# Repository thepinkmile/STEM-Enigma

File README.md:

# STEM-Enigma
A repository containing data, designs and software for an Enigma Machine.

## Interactive 3D Enigma

The existing [Code Breakers application](Software/APP-CodeBreakers/src/CodeBreakers/README.md)
uses Avalonia and TinyFFR to animate rotor gears, trace electrical connections,
and switch between assembled and exploded views. Original part models and
their generator are included.

With the .NET 10 SDK installed:

```powershell
Set-Location Software\APP-CodeBreakers\src
dotnet run --project CodeBreakers.Desktop
```

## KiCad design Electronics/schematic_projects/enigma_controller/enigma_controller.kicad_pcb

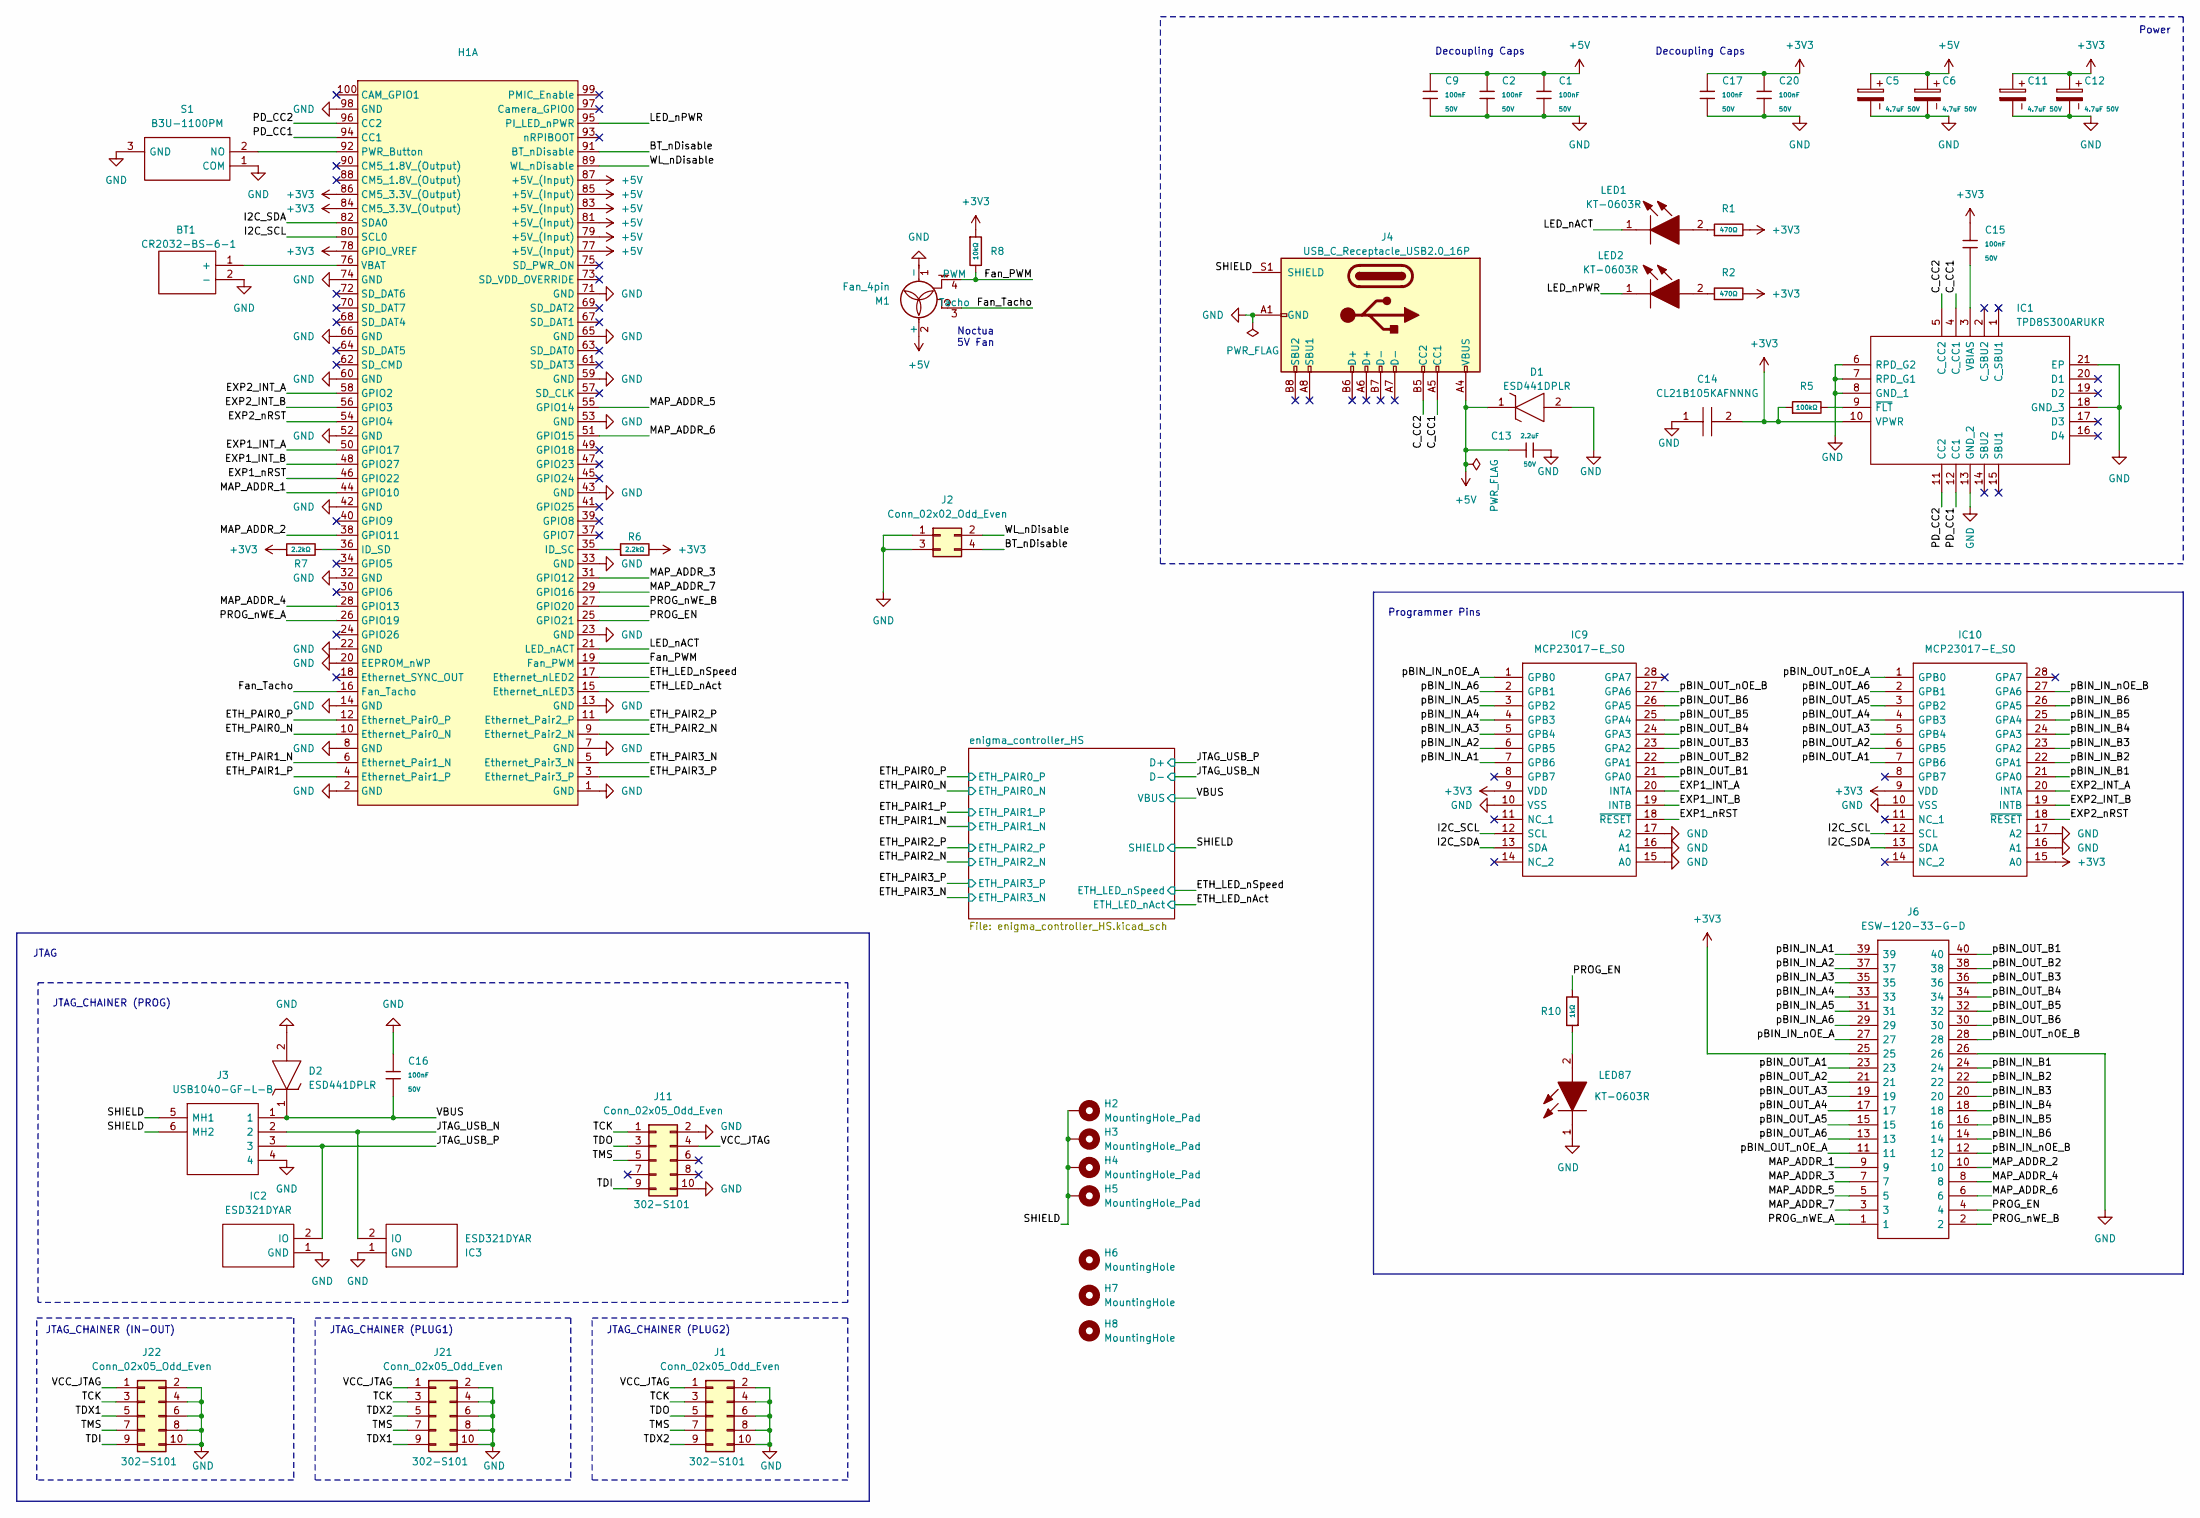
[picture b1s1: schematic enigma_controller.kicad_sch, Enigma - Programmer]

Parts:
BT1: CR2032-BS-6-1; CR2032BS61; Manufacturer_Part_Number CR2032-BS-6-1
C1, C2, C9, C15, C16, C17, C20: 100nF; C_0402; Voltage Rated 50V; Tolerance ±10%; Part CL05B104KB54PNC; LCSC C307331
C5, C6, C11, C12: 4.7uF 50V; CP_Radial_D5.0mm_P2.00mm
C13: 2.2uF; C_1206; Voltage Rated 50V; Tolerance ±10%; Part CL31B225KBHNNNE; LCSC C50254
C14: CL21B105KAFNNNG; CAPC2012X135N; Manufacturer_Part_Number CL21B105KAFNNNG; Mouser Part Number 187-CL21B105KAFNNNG
D1, D2: ESD441DPLR; Manufacturer_Part_Number ESD441DPLR; Mouser Part Number 595-ESD441DPLR
H1: RaspberryPi-CM5-Carrier-Tall-Pad-Via-Standoff
H2, H3, H4, H5: MountingHole_Pad; MountingHole_4.3mm_M4_Pad_Via
H6, H7, H8: MountingHole; MountingHole_4.3mm_M4
IC1: TPD8S300ARUKR; QFN40P300X300X80-21N-D; Manufacturer_Part_Number TPD8S300ARUKR; Mouser Part Number 595-TPD8S300ARUKR
IC2, IC3: ESD321DYAR; SODFL1608X77N; Manufacturer_Part_Number ESD321DYAR; Mouser Part Number 595-ESD321DYAR
IC9, IC10: MCP23017-E_SO; SOIC127P1030X265-28N; Manufacturer_Part_Number MCP23017-E/SO; Mouser Part Number 579-MCP23017-E/SO
J1, J21, J22: Conn_02x05_Odd_Even; IDC-Header_2x05_P2.54mm_Horizontal; Part No 302-S101; DigiKey Part No ED1543-ND
J2: Conn_02x02_Odd_Even; PinHeader_2x02_P2.54mm_Vertical
J3: USB1040-GF-L-B; USB1040GFLB; Manufacturer_Part_Number USB1040-GF-L-B; Mouser Part Number 640-USB1040-GF-L-B
J4: USB_C_Receptacle_USB2.0_16P; USB_C_Receptacle_Amphenol_124019772112A; LCSC C5430474
J6: ESW-120-33-G-D; ESW-120-XX-Y-D; Manufacturer_Part_Number ESW-120-33-G-D; Mouser Part Number 200-ESW12033GD
J11: Conn_02x05_Odd_Even; IDC-Header_2x05_P2.54mm_Vertical; Part No 302-S101; DigiKey Part No ED1543-ND
LED1, LED2, LED87: KT-0603R; LEDC1608X70N; Manufacturer_Part_Number KT-0603R
M1: Fan_4pin; FanPinHeader_1x04_P2.54mm_Vertical
R1, R2: 470Ω; R_0402; Overload Voltage (Max) 50V; Tolerance ±1%; Part 0402WGF4700TCE; LCSC C25117
R5: 100kΩ; R_0402; Overload Voltage (Max) 50V; Tolerance ±1%; Part 0402WGF1003TCE; LCSC C25741
R6, R7: 2.2kΩ; R_0402; Overload Voltage (Max) 50V; Tolerance ±1%; Part 0402WGF2201TCE; LCSC C25879
R8: 10kΩ; R_0402; Overload Voltage (Max) 50V; Tolerance ±1%; Part 0402WGF1002TCE; LCSC C25744
R10: 1kΩ; R_0402; Overload Voltage (Max) 50V; Tolerance ±1%; Part 0402WGF1001TCE; LCSC C11702
S1: B3U-1100PM; B3U1100PM; Manufacturer_Part_Number B3U-1100PM; Mouser Part Number 653-B3U-1100PM

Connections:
+3V3: C11.1, C12.1, C14.2, C15.1, C17.1, C20.1, H1.78 (GPIO_VREF), H1.84 (CM5_3.3V_(Output)), H1.86 (CM5_3.3V_(Output)), IC1.10 (VPWR), IC9.9 (VDD), IC10.9 (VDD), IC10.15 (A0), J6.25, R1.2, R2.2, R5.1, R6.2, R7.1, R8.1; also elsewhere on the board
+5V: C1.1, C2.1, C5.1, C6.1, C9.1, C13.1, D1.1, H1.77 (+5V_(Input)), H1.79 (+5V_(Input)), H1.81 (+5V_(Input)), H1.83 (+5V_(Input)), H1.85 (+5V_(Input)), H1.87 (+5V_(Input)), J4.A4 (VBUS), J4.A9 (VBUS), J4.B4 (VBUS), J4.B9 (VBUS), M1.2 (+); also elsewhere on the board
/BT_nDisable: H1.91 (BT_nDisable), J2.4
/C_CC1: IC1.4 (C_CC1), J4.A5 (CC1)
/C_CC2: IC1.5 (C_CC2), J4.B5 (CC2)
/ETH_LED_nAct: H1.15 (Ethernet_nLED3); also elsewhere on the board
/ETH_LED_nSpeed: H1.17 (Ethernet_nLED2); also elsewhere on the board
/ETH_PAIR0_N: H1.10 (Ethernet_Pair0_N); also elsewhere on the board
/ETH_PAIR0_P: H1.12 (Ethernet_Pair0_P); also elsewhere on the board
/ETH_PAIR1_N: H1.6 (Ethernet_Pair1_N); also elsewhere on the board
/ETH_PAIR1_P: H1.4 (Ethernet_Pair1_P); also elsewhere on the board
/ETH_PAIR2_N: H1.9 (Ethernet_Pair2_N); also elsewhere on the board
/ETH_PAIR2_P: H1.11 (Ethernet_Pair2_P); also elsewhere on the board
/ETH_PAIR3_N: H1.5 (Ethernet_Pair3_N); also elsewhere on the board
/ETH_PAIR3_P: H1.3 (Ethernet_Pair3_P); also elsewhere on the board
/EXP1_INT_A: H1.50 (GPIO17), IC9.20 (INTA)
/EXP1_INT_B: H1.48 (GPIO27), IC9.19 (INTB)
/EXP1_nRST: H1.46 (GPIO22), IC9.18 (~RESET)
/EXP2_INT_A: H1.58 (GPIO2), IC10.20 (INTA)
/EXP2_INT_B: H1.56 (GPIO3), IC10.19 (INTB)
/EXP2_nRST: H1.54 (GPIO4), IC10.18 (~RESET)
/Fan_PWM: H1.19 (Fan_PWM), M1.4 (PWM), R8.2
/Fan_Tacho: H1.16 (Fan_Tacho), M1.3 (Tacho)
/I2C_SCL: H1.80 (SCL0), IC9.12 (SCL), IC10.12 (SCL)
/I2C_SDA: H1.82 (SDA0), IC9.13 (SDA), IC10.13 (SDA)
/JTAG_USB_N: IC3.2 (IO), J3.2; also elsewhere on the board
/JTAG_USB_P: IC2.2 (IO), J3.3; also elsewhere on the board
/LED_nACT: H1.21 (LED_nACT), LED1.1
/LED_nPWR: H1.95 (PI_LED_nPWR), LED2.1
/MAP_ADDR_1: H1.44 (GPIO10), J6.9
/MAP_ADDR_2: H1.38 (GPIO11), J6.10
/MAP_ADDR_3: H1.31 (GPIO12), J6.7
/MAP_ADDR_4: H1.28 (GPIO13), J6.8
/MAP_ADDR_5: H1.55 (GPIO14), J6.5
/MAP_ADDR_6: H1.51 (GPIO15), J6.6
/MAP_ADDR_7: H1.29 (GPIO16), J6.3
/PD_CC1: H1.94 (CC1), IC1.12 (CC1)
/PD_CC2: H1.96 (CC2), IC1.11 (CC2)
/PROG_EN: H1.25 (GPIO21), J6.4, R10.2
/PROG_nWE_A: H1.26 (GPIO19), J6.1
/PROG_nWE_B: H1.27 (GPIO20), J6.2
/SHIELD: H2.1, H3.1, H4.1, H5.1, J3.5 (MH1), J3.6 (MH2), J4.S1 (SHIELD); also elsewhere on the board
/TCK: J1.3, J11.1, J21.3, J22.3
/TDI: J11.9, J22.9
/TDO: J1.5, J11.3
/TDX1: J21.9, J22.5
/TDX2: J1.9, J21.5
/TMS: J1.7, J11.5, J21.7, J22.7
/VBUS: C16.2, D2.1, J3.1; also elsewhere on the board
/VCC_JTAG: J1.1, J11.4, J21.1, J22.1
/WL_nDisable: H1.89 (WL_nDisable), J2.2
/pBIN_IN_A1: IC9.7 (GPB6), J6.39
/pBIN_IN_A2: IC9.6 (GPB5), J6.37
/pBIN_IN_A3: IC9.5 (GPB4), J6.35
/pBIN_IN_A4: IC9.4 (GPB3), J6.33
/pBIN_IN_A5: IC9.3 (GPB2), J6.31
/pBIN_IN_A6: IC9.2 (GPB1), J6.29
/pBIN_IN_B1: IC10.21 (GPA0), J6.24
/pBIN_IN_B2: IC10.22 (GPA1), J6.22
/pBIN_IN_B3: IC10.23 (GPA2), J6.20
/pBIN_IN_B4: IC10.24 (GPA3), J6.18
/pBIN_IN_B5: IC10.25 (GPA4), J6.16
/pBIN_IN_B6: IC10.26 (GPA5), J6.14
/pBIN_IN_nOE_A: IC9.1 (GPB0), J6.27
/pBIN_IN_nOE_B: IC10.27 (GPA6), J6.12
/pBIN_OUT_A1: IC10.7 (GPB6), J6.23
/pBIN_OUT_A2: IC10.6 (GPB5), J6.21
/pBIN_OUT_A3: IC10.5 (GPB4), J6.19
/pBIN_OUT_A4: IC10.4 (GPB3), J6.17
/pBIN_OUT_A5: IC10.3 (GPB2), J6.15
/pBIN_OUT_A6: IC10.2 (GPB1), J6.13
/pBIN_OUT_B1: IC9.21 (GPA0), J6.40
/pBIN_OUT_B2: IC9.22 (GPA1), J6.38
/pBIN_OUT_B3: IC9.23 (GPA2), J6.36
/pBIN_OUT_B4: IC9.24 (GPA3), J6.34
/pBIN_OUT_B5: IC9.25 (GPA4), J6.32
/pBIN_OUT_B6: IC9.26 (GPA5), J6.30
/pBIN_OUT_nOE_A: IC10.1 (GPB0), J6.11
/pBIN_OUT_nOE_B: IC9.27 (GPA6), J6.28
GND: BT1.2 (-), C1.2, C2.2, C5.2, C6.2, C9.2, C11.2, C12.2, C13.2, C14.1, C16.1, C17.2, C20.2, D1.2, D2.2, H1.1 (GND), H1.2 (GND), H1.7 (GND), H1.8 (GND), H1.13 (GND), H1.14 (GND), H1.20 (EEPROM_nWP), H1.22 (GND), H1.23 (GND), H1.32 (GND), H1.33 (GND), H1.42 (GND), H1.43 (GND), H1.52 (GND), H1.53 (GND), H1.59 (GND), H1.60 (GND), H1.65 (GND), H1.66 (GND), H1.71 (GND), H1.74 (GND), H1.98 (GND), IC1.6 (RPD_G2), IC1.7 (RPD_G1), IC1.8 (GND_1), IC1.13 (GND_2), IC1.18 (GND_3), IC1.21 (EP), IC2.1 (GND), IC3.1 (GND), IC9.10 (VSS), IC9.15 (A0), IC9.16 (A1), IC9.17 (A2), IC10.10 (VSS), IC10.16 (A1), IC10.17 (A2), J1.2, J1.4, J1.6, J1.8, J1.10, J2.1, J2.3, J3.4, J4.A1 (GND), J4.A12 (GND), J4.B1 (GND), J4.B12 (GND), J6.26, J11.2, J11.10, J21.2, J21.4, J21.6, J21.8, J21.10, J22.2, J22.4, J22.6, J22.8, J22.10, LED87.1, M1.1 (-), S1.1 (COM), S1.3 (GND); also elsewhere on the board
unnamed: BT1.1 (+), H1.76 (VBAT)
unnamed: H1.35 (ID_SC), R6.1
unnamed: H1.36 (ID_SD), R7.2
unnamed: H1.92 (PWR_Button), S1.2 (NO)
unnamed: C15.2, IC1.3 (VBIAS)
unnamed: IC1.9 (~FLT), R5.2
unnamed: LED1.2, R1.1
unnamed: LED2.2, R2.1
unnamed: LED87.2, R10.1

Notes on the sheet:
Power
Decoupling Caps
JTAG_CHAINER (IN-OUT)
JTAG
Noctua 5V Fan
Programmer Pins
JTAG_CHAINER (PLUG2)
JTAG_CHAINER (PLUG1)
JTAG_CHAINER (PROG)

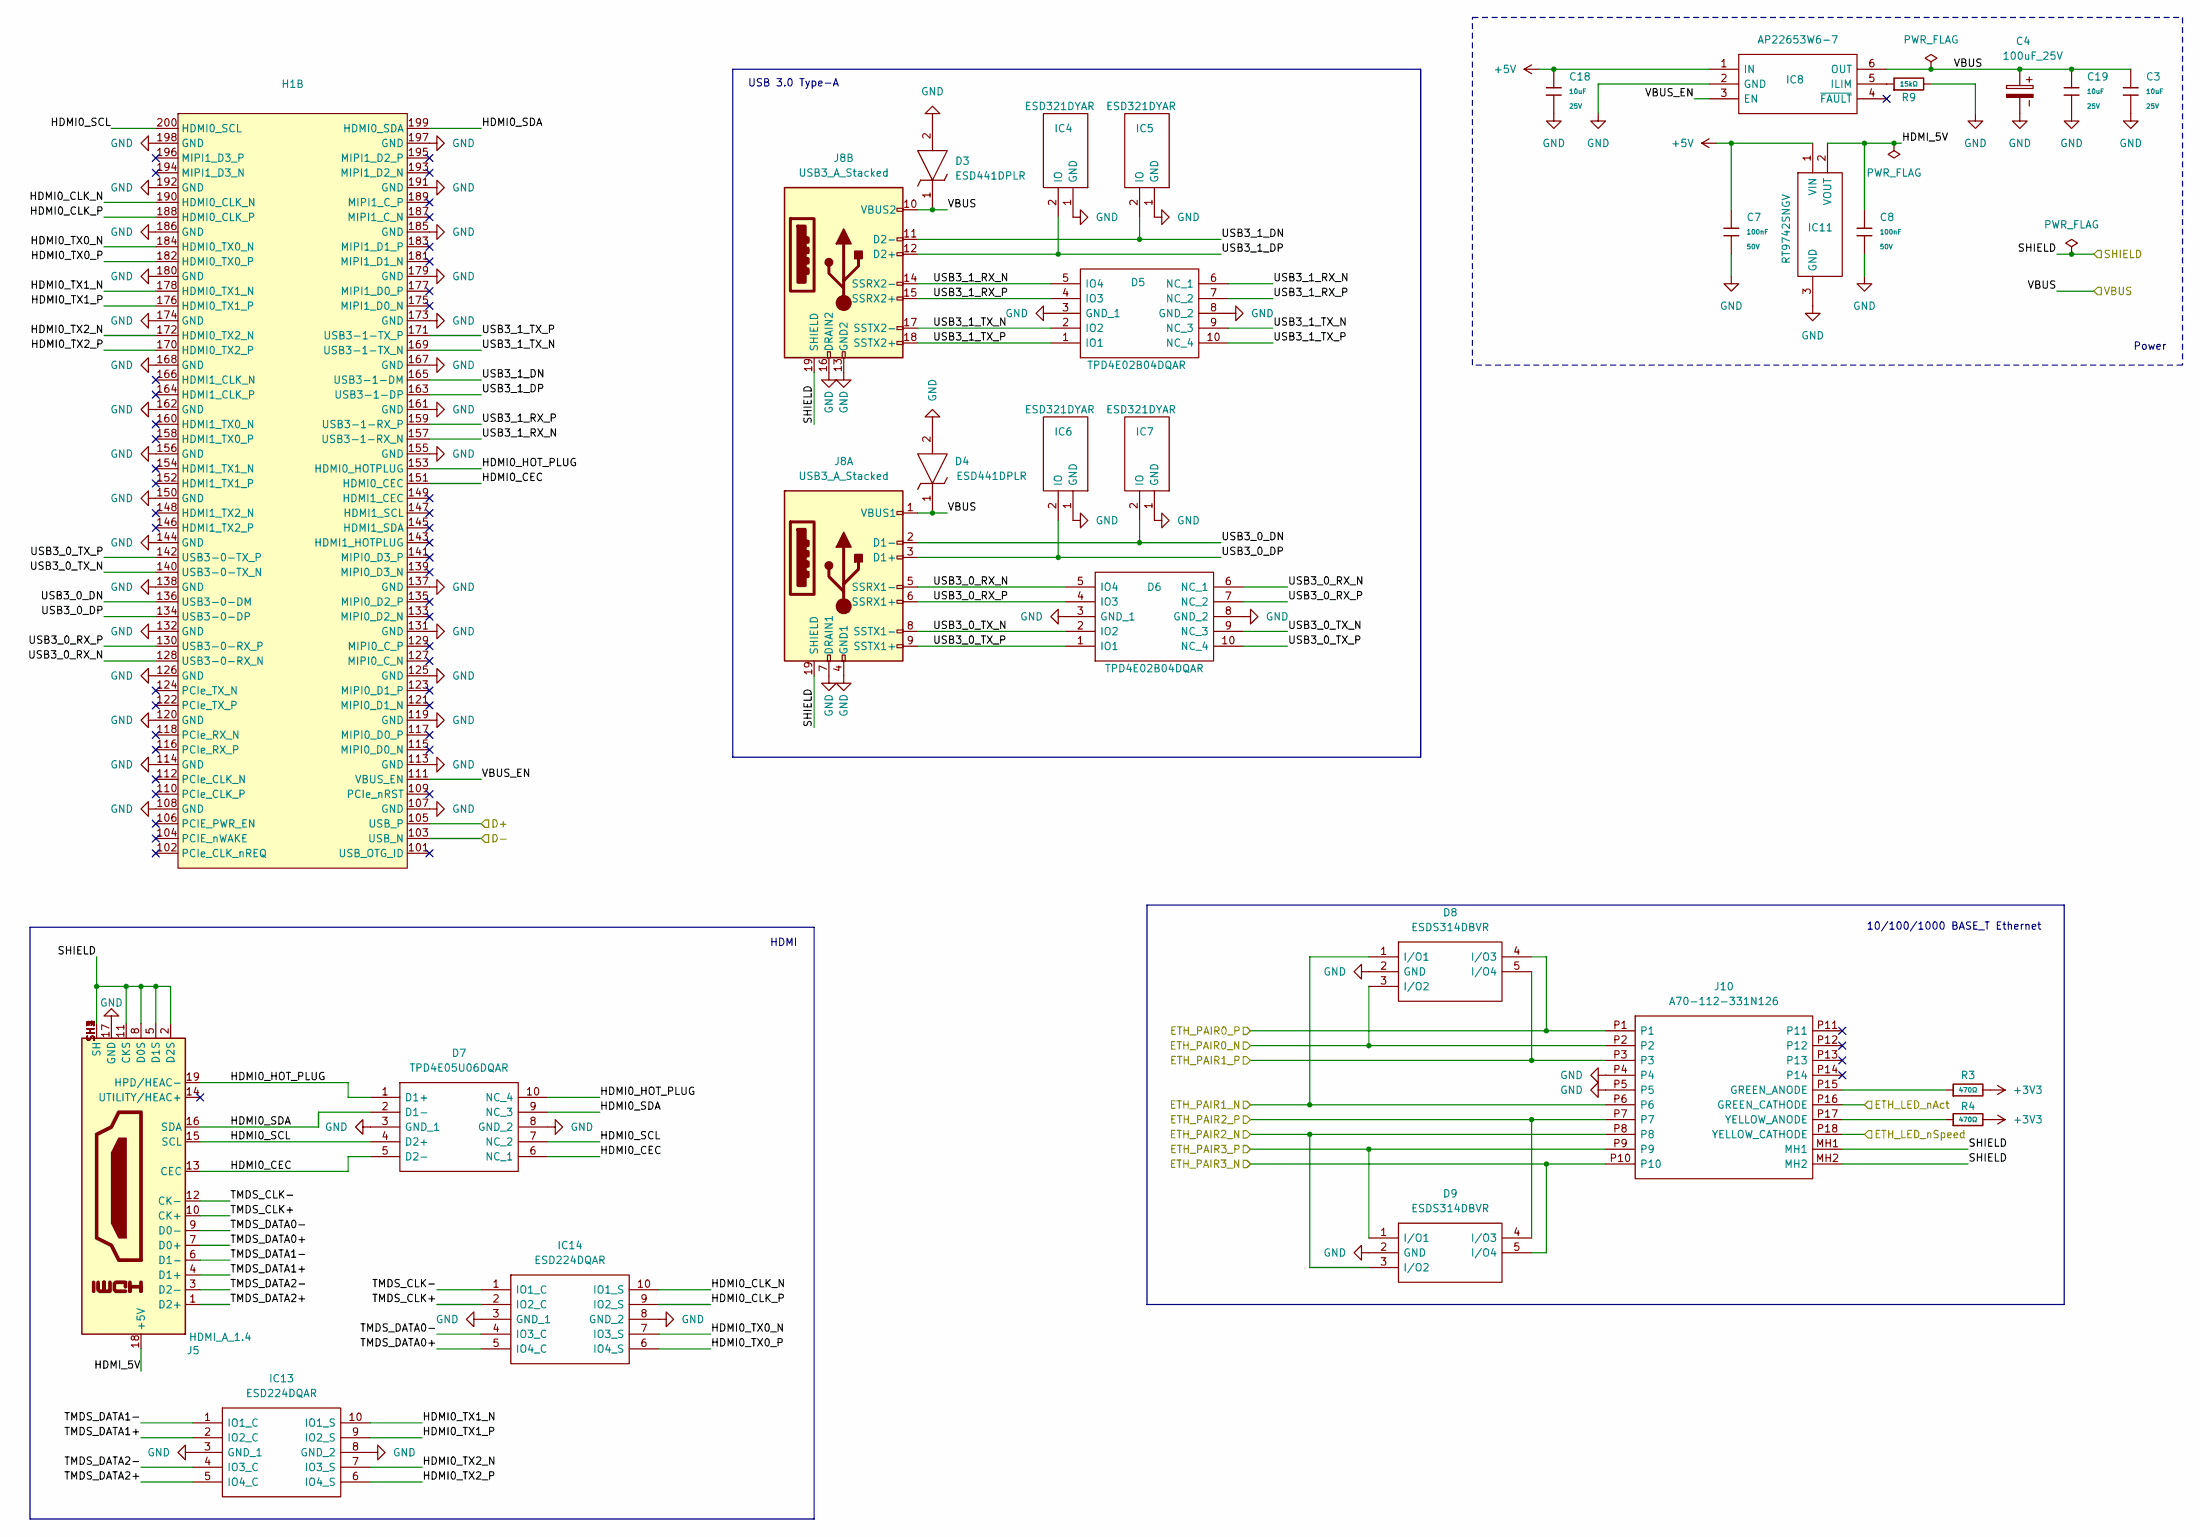
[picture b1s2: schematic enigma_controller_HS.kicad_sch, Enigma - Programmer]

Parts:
C3, C18, C19: 10uF; C_0603; Voltage Rated 25V; Tolerance ±20%; Part CL10A106MA8NRNC; LCSC C96446
C4: 100uF_25V; CP_Radial_D6.3mm_P2.50mm
C7, C8: 100nF; C_0402; Voltage Rated 50V; Tolerance ±10%; Part CL05B104KB54PNC; LCSC C307331
D3, D4: ESD441DPLR; Manufacturer_Part_Number ESD441DPLR; Mouser Part Number 595-ESD441DPLR
D5, D6: TPD4E02B04DQAR; DQA(R-PUSON-N10); Manufacturer_Part_Number TPD4E02B04DQAR; Mouser Part Number 595-TPD4E02B04DQAR
D7: TPD4E05U06DQAR; DQA(R-PUSON-N10); Manufacturer_Part_Number TPD4E05U06DQAR; Mouser Part Number 595-TPD4E05U06DQAR
D8, D9: ESDS314DBVR; SOT95P280X145-5N; Manufacturer_Part_Number ESDS314DBVR; Mouser Part Number 595-ESDS314DBVR
H1: RaspberryPi-CM5-Carrier-Tall-Pad-Via-Standoff
IC4, IC5, IC6, IC7: ESD321DYAR; SODFL1608X77N; Manufacturer_Part_Number ESD321DYAR; Mouser Part Number 595-ESD321DYAR
IC8: AP22653W6-7; SOT95P280X145-6N; Manufacturer_Part_Number AP22653W6-7; Mouser Part Number 621-AP22653W6-7
IC11: RT9742SNGV; SOT95P279X130-3N; Manufacturer_Part_Number RT9742SNGV; Mouser Part Number 835-RT9742SNGV
IC13, IC14: ESD224DQAR; Manufacturer_Part_Number ESD224DQAR; Mouser Part Number 595-ESD224DQAR
J5: HDMI_A_1.4; EDAC 690-019-298-412
J8: USB3_A_Stacked; USB3_A_Molex_48406-0001_Horizontal_Stacked
J10: A70-112-331N126; A70112331N126; Manufacturer_Part_Number A70-112-331N126
R3, R4: 470Ω; R_0402; Overload Voltage (Max) 50V; Tolerance ±1%; Part 0402WGF4700TCE; LCSC C25117
R9: 15kΩ; R_0402; Overload Voltage (Max) 50V; Tolerance ±1%; Part 0402WGF1502TCE; LCSC C25756

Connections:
+3V3: R3.2, R4.2; also elsewhere on the board
+5V: C7.1, C18.1, IC8.1 (IN), IC11.1 (VIN); also elsewhere on the board
/ETH_LED_nAct: J10.P16 (GREEN_CATHODE); also elsewhere on the board
/ETH_LED_nSpeed: J10.P18 (YELLOW_CATHODE); also elsewhere on the board
/ETH_PAIR0_N: D8.3 (I/O2), J10.P2; also elsewhere on the board
/ETH_PAIR0_P: D8.4 (I/O3), J10.P1; also elsewhere on the board
/ETH_PAIR1_N: D8.1 (I/O1), J10.P6; also elsewhere on the board
/ETH_PAIR1_P: D8.5 (I/O4), J10.P3; also elsewhere on the board
/ETH_PAIR2_N: D9.3 (I/O2), J10.P8; also elsewhere on the board
/ETH_PAIR2_P: D9.4 (I/O3), J10.P7; also elsewhere on the board
/ETH_PAIR3_N: D9.5 (I/O4), J10.P10; also elsewhere on the board
/ETH_PAIR3_P: D9.1 (I/O1), J10.P9; also elsewhere on the board
/JTAG_USB_N: H1.103 (USB_N); also elsewhere on the board
/JTAG_USB_P: H1.105 (USB_P); also elsewhere on the board
/SHIELD: J5.2 (D2S), J5.5 (D1S), J5.8 (D0S), J5.11 (CKS), J5.SH1 (SH), J5.SH2 (SH), J5.SH3 (SH), J5.SH4 (SH), J8.19 (SHIELD), J10.MH1, J10.MH2; also elsewhere on the board
/VBUS: C3.1, C4.1, C19.1, D3.1, D4.1, IC8.6 (OUT), J8.1 (VBUS1), J8.10 (VBUS2); also elsewhere on the board
/enigma_controller_HS/HDMI0_CEC: D7.5 (D2-), D7.6 (NC_1), H1.151 (HDMI0_CEC), J5.13 (CEC)
/enigma_controller_HS/HDMI0_CLK_N: H1.190 (HDMI0_CLK_N), IC14.10 (IO1_S)
/enigma_controller_HS/HDMI0_CLK_P: H1.188 (HDMI0_CLK_P), IC14.9 (IO2_S)
/enigma_controller_HS/HDMI0_HOT_PLUG: D7.1 (D1+), D7.10 (NC_4), H1.153 (HDMI0_HOTPLUG), J5.19 (HPD/HEAC-)
/enigma_controller_HS/HDMI0_SCL: D7.4 (D2+), D7.7 (NC_2), H1.200 (HDMI0_SCL), J5.15 (SCL)
/enigma_controller_HS/HDMI0_SDA: D7.2 (D1-), D7.9 (NC_3), H1.199 (HDMI0_SDA), J5.16 (SDA)
/enigma_controller_HS/HDMI0_TX0_N: H1.184 (HDMI0_TX0_N), IC14.7 (IO3_S)
/enigma_controller_HS/HDMI0_TX0_P: H1.182 (HDMI0_TX0_P), IC14.6 (IO4_S)
/enigma_controller_HS/HDMI0_TX1_N: H1.178 (HDMI0_TX1_N), IC13.10 (IO1_S)
/enigma_controller_HS/HDMI0_TX1_P: H1.176 (HDMI0_TX1_P), IC13.9 (IO2_S)
/enigma_controller_HS/HDMI0_TX2_N: H1.172 (HDMI0_TX2_N), IC13.7 (IO3_S)
/enigma_controller_HS/HDMI0_TX2_P: H1.170 (HDMI0_TX2_P), IC13.6 (IO4_S)
/enigma_controller_HS/HDMI_5V: C8.1, IC11.2 (VOUT), J5.18 (+5V)
/enigma_controller_HS/TMDS_CLK+: IC14.2 (IO2_C), J5.10 (CK+)
/enigma_controller_HS/TMDS_CLK-: IC14.1 (IO1_C), J5.12 (CK-)
/enigma_controller_HS/TMDS_DATA0+: IC14.5 (IO4_C), J5.7 (D0+)
/enigma_controller_HS/TMDS_DATA0-: IC14.4 (IO3_C), J5.9 (D0-)
/enigma_controller_HS/TMDS_DATA1+: IC13.2 (IO2_C), J5.4 (D1+)
/enigma_controller_HS/TMDS_DATA1-: IC13.1 (IO1_C), J5.6 (D1-)
/enigma_controller_HS/TMDS_DATA2+: IC13.5 (IO4_C), J5.1 (D2+)
/enigma_controller_HS/TMDS_DATA2-: IC13.4 (IO3_C), J5.3 (D2-)
/enigma_controller_HS/USB3_0_DN: H1.136 (USB3-0-DM), IC7.2 (IO), J8.2 (D1-)
/enigma_controller_HS/USB3_0_DP: H1.134 (USB3-0-DP), IC6.2 (IO), J8.3 (D1+)
/enigma_controller_HS/USB3_0_RX_N: D6.5 (IO4), D6.6 (NC_1), H1.128 (USB3-0-RX_N), J8.5 (SSRX1-)
/enigma_controller_HS/USB3_0_RX_P: D6.4 (IO3), D6.7 (NC_2), H1.130 (USB3-0-RX_P), J8.6 (SSRX1+)
/enigma_controller_HS/USB3_0_TX_N: D6.2 (IO2), D6.9 (NC_3), H1.140 (USB3-0-TX_N), J8.8 (SSTX1-)
/enigma_controller_HS/USB3_0_TX_P: D6.1 (IO1), D6.10 (NC_4), H1.142 (USB3-0-TX_P), J8.9 (SSTX1+)
/enigma_controller_HS/USB3_1_DN: H1.165 (USB3-1-DM), IC5.2 (IO), J8.11 (D2-)
/enigma_controller_HS/USB3_1_DP: H1.163 (USB3-1-DP), IC4.2 (IO), J8.12 (D2+)
/enigma_controller_HS/USB3_1_RX_N: D5.5 (IO4), D5.6 (NC_1), H1.157 (USB3-1-RX_N), J8.14 (SSRX2-)
/enigma_controller_HS/USB3_1_RX_P: D5.4 (IO3), D5.7 (NC_2), H1.159 (USB3-1-RX_P), J8.15 (SSRX2+)
/enigma_controller_HS/USB3_1_TX_N: D5.2 (IO2), D5.9 (NC_3), H1.169 (USB3-1-TX_N), J8.17 (SSTX2-)
/enigma_controller_HS/USB3_1_TX_P: D5.1 (IO1), D5.10 (NC_4), H1.171 (USB3-1-TX_P), J8.18 (SSTX2+)
/enigma_controller_HS/VBUS_EN: H1.111 (VBUS_EN), IC8.3 (EN)
GND: C3.2, C4.2, C7.2, C8.2, C18.2, C19.2, D3.2, D4.2, D5.3 (GND_1), D5.8 (GND_2), D6.3 (GND_1), D6.8 (GND_2), D7.3 (GND_1), D7.8 (GND_2), D8.2 (GND), D9.2 (GND), H1.107 (GND), H1.108 (GND), H1.113 (GND), H1.114 (GND), H1.119 (GND), H1.120 (GND), H1.125 (GND), H1.126 (GND), H1.131 (GND), H1.132 (GND), H1.137 (GND), H1.138 (GND), H1.144 (GND), H1.150 (GND), H1.155 (GND), H1.156 (GND), H1.161 (GND), H1.162 (GND), H1.167 (GND), H1.168 (GND), H1.173 (GND), H1.174 (GND), H1.179 (GND), H1.180 (GND), H1.185 (GND), H1.186 (GND), H1.191 (GND), H1.192 (GND), H1.197 (GND), H1.198 (GND), IC4.1 (GND), IC5.1 (GND), IC6.1 (GND), IC7.1 (GND), IC8.2 (GND), IC11.3 (GND), IC13.3 (GND_1), IC13.8 (GND_2), IC14.3 (GND_1), IC14.8 (GND_2), J5.17 (GND), J8.4 (GND1), J8.7 (DRAIN1), J8.13 (GND2), J8.16 (DRAIN2), J10.P4, J10.P5, R9.2; also elsewhere on the board
unnamed: IC8.5 (ILIM), R9.1
unnamed: J10.P15 (GREEN_ANODE), R3.1
unnamed: J10.P17 (YELLOW_ANODE), R4.1

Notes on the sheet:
10/100/1000 BASE_T Ethernet
USB 3.0 Type-A
Power
HDMI

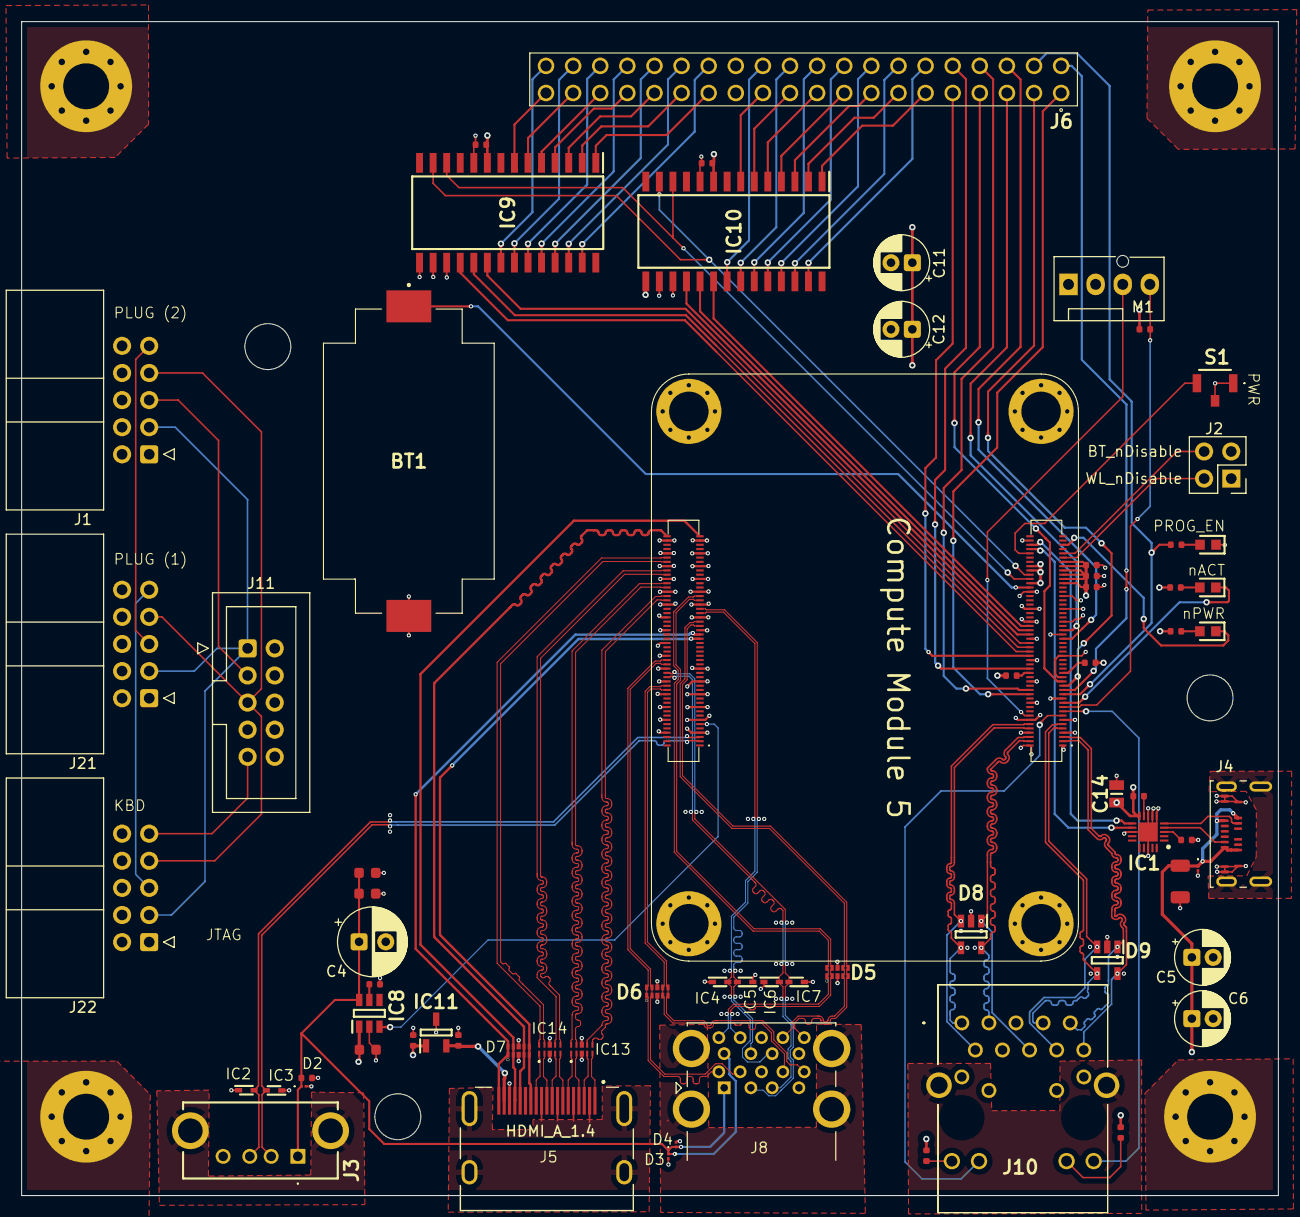
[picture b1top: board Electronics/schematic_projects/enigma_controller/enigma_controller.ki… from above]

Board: 6 copper layers, 117.7 x 110.0 mm, 76 parts (0 on the bottom side), 126 nets.

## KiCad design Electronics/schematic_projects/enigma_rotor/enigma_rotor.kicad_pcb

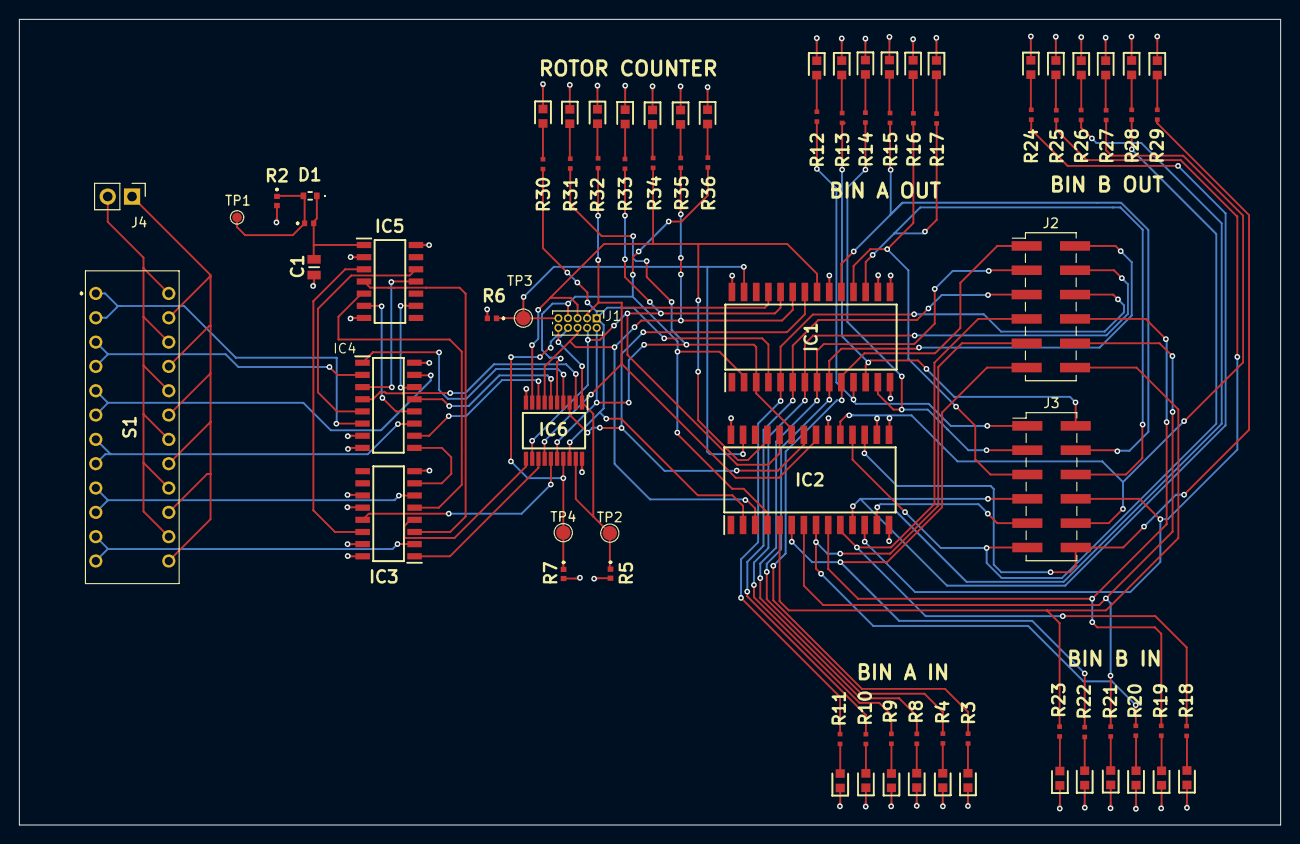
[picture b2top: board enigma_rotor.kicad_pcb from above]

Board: 4 copper layers, 131.7 x 84.1 mm, 84 parts (0 on the bottom side), 91 nets.

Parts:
C1: CL21B105KAFNNNG; CAPC2012X135N
D1: 1N4148WT-7; 1N4148WT7
IC1, IC2: AT28BV64B-20SU-T; SOIC127P1032X265-28N
IC3, IC4: CD74HC283M96; SOIC127P600X175-16N
IC5: CD74HC4024M96; SOIC127P600X175-14N
IC6: SN74LVCH244APWR; SOP65P640X120-20N
J1: Conn_02x05_Odd_Even; PinHeader_2x05_P1.00mm_Vertical
J2, J3: Conn_02x06_Top_Bottom; PinHeader_2x06_P2.54mm_Vertical_SMD
J4: Conn_01x02; PinHeader_1x02_P2.54mm_Vertical
LED1, LED2, LED3, LED4, LED5, LED6, LED7, LED8, LED9, LED10, LED11, LED12, LED13, LED14, LED15, LED16, LED17, LED18, LED19, LED20, LED21, LED22, LED23, LED24, LED25, LED26, LED27, LED28, LED29, LED30, LED31: KT-0603R; LEDC1608X70N
R1: MCS04020D2202BE100; MCS04020C1003FE000
R2: MCS04020C5102FE000; MCS04020C1003FE000
R3, R4, R8, R9, R10, R11, R12, R13, R14, R15, R16, R17, R18, R19, R20, R21, R22, R23, R24, R25, R26, R27, R28, R29, R30, R31, R32, R33, R34, R35, R36: ERA2AEB201X; ERA2AED122X
R5, R6, R7: MCS0402MD1002BE100; MCS04020C1003FE000
S1: 206-126; 206126
TP1: TestPoint_Small; TestPoint_Pad_D1.0mm
TP2, TP3, TP4: TestPoint_Small; TestPoint_Pad_D1.5mm

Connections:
/BIN_IN_A1: IC1.10 (A0), J2.1, R3.2
/BIN_IN_A2: IC1.9 (A1), J2.2, R4.2
/BIN_IN_A3: IC1.8 (A2), J2.3, R8.2
/BIN_IN_A4: IC1.7 (A3), J2.4, R9.2
/BIN_IN_A5: IC1.6 (A4), J2.5, R10.2
/BIN_IN_A6: IC1.5 (A5), J2.6, R11.2
/BIN_IN_B1: IC2.10 (A0), J2.7, R18.2
/BIN_IN_B2: IC2.9 (A1), J2.8, R19.2
/BIN_IN_B3: IC2.8 (A2), J2.9, R20.2
/BIN_IN_B4: IC2.7 (A3), J2.10, R21.2
/BIN_IN_B5: IC2.6 (A4), J2.11, R22.2
/BIN_IN_B6: IC2.5 (A5), J2.12, R23.2
/BIN_OUT_A1: IC1.11 (I/O0), J3.1, R12.2
/BIN_OUT_A2: IC1.12 (I/O1), J3.2, R13.2
/BIN_OUT_A3: IC1.13 (I/O2), J3.3, R14.2
/BIN_OUT_A4: IC1.19 (I/O7), J3.4, R15.2
/BIN_OUT_A5: IC1.18 (I/O6), J3.5, R16.2
/BIN_OUT_A6: IC1.17 (I/O5), J3.6, R17.2
/BIN_OUT_B1: IC2.11 (I/O0), J3.7, R24.2
/BIN_OUT_B2: IC2.12 (I/O1), J3.8, R25.2
/BIN_OUT_B3: IC2.13 (I/O2), J3.9, R26.2
/BIN_OUT_B4: IC2.19 (I/O7), J3.10, R27.2
/BIN_OUT_B5: IC2.18 (I/O6), J3.11, R28.2
/BIN_OUT_B6: IC2.17 (I/O5), J3.12, R29.2
/CNT_OUT_1: IC4.5 (A0), IC5.12 (Q1)
/CNT_OUT_2: IC4.3 (A1), IC5.11 (Q2)
/CNT_OUT_3: IC4.14 (A2), IC5.9 (Q3)
/CNT_OUT_4: IC4.12 (A3), IC5.6 (Q4)
/CNT_OUT_5: IC3.5 (A0), IC5.5 (Q5)
/CNT_OUT_6: IC3.3 (A1), IC5.4 (Q6)
/CNT_OUT_7: IC3.14 (A2), IC5.3 (Q7)
/MAP_ADDR_1: IC1.4 (A6), IC2.2 (A12), IC6.18 (1Y1), J1.1, R30.2
/MAP_ADDR_2: IC1.3 (A7), IC2.23 (A11), IC6.16 (1Y2), J1.2, R31.2
/MAP_ADDR_3: IC1.25 (A8), IC2.21 (A10), IC6.14 (1Y3), J1.3, R32.2
/MAP_ADDR_4: IC1.24 (A9), IC2.24 (A9), IC6.12 (1Y4), J1.4, R33.2
/MAP_ADDR_5: IC1.21 (A10), IC2.25 (A8), IC6.9 (2Y1), J1.5, R34.2
/MAP_ADDR_6: IC1.23 (A11), IC2.3 (A7), IC6.7 (2Y2), J1.6, R35.2
/MAP_ADDR_7: IC1.2 (A12), IC2.4 (A6), IC6.5 (2Y3), J1.7, R36.2
/MAP_IN_1: IC4.4 (S0), IC6.2 (1A1)
/MAP_IN_2: IC4.1 (S1), IC6.4 (1A2)
/MAP_IN_3: IC4.13 (S2), IC6.6 (1A3)
/MAP_IN_4: IC4.10 (S3), IC6.8 (1A4)
/MAP_IN_5: IC3.4 (S0), IC6.11 (2A1)
/MAP_IN_6: IC3.1 (S1), IC6.13 (2A2)
/MAP_IN_7: IC3.13 (S2), IC6.15 (2A3)
/OUT_EN: IC1.22 (~OE), IC2.22 (~OE), IC6.3 (2Y4)
/PRE_SET_1: IC4.6 (B0), S1.1 (COM_1), S1.2 (COM_2)
/PRE_SET_2: IC4.2 (B1), S1.5 (COM_3), S1.6 (COM_4)
/PRE_SET_3: IC4.15 (B2), S1.9 (COM_5), S1.10 (COM_6)
/PRE_SET_4: IC4.11 (B3), S1.13 (COM_7), S1.14 (COM_8)
/PRE_SET_5: IC3.6 (B0), S1.17 (COM_9), S1.18 (COM_10)
/PRE_SET_6: IC3.2 (B1), S1.21 (COM_11), S1.22 (COM_12)
/PROG_EN: IC6.1 (1~OE), IC6.19 (2~OE), J1.10, R5.1, TP2.1
/PROG_READ_EN: IC6.17 (2A4), J1.8, R7.1, TP4.1
/PROG_WRITE_EN: IC1.27 (~WE), IC2.27 (~WE), J1.9, R6.1, TP3.1
GND: C1.1, IC1.14 (GND), IC1.15 (I/O3), IC1.16 (I/O4), IC1.20 (~CE), IC2.14 (GND), IC2.15 (I/O3), IC2.16 (I/O4), IC2.20 (~CE), IC3.8 (GND), IC3.11 (B3), IC3.12 (A3), IC3.15 (B2), IC4.7 (CIN), IC4.8 (GND), IC5.2 (MR), IC5.7 (GND), IC6.10 (GND), J4.2, LED1.1, LED2.1, LED3.1, LED4.1, LED5.1, LED6.1, LED7.1, LED8.1, LED9.1, LED10.1, LED11.1, LED12.1, LED13.1, LED14.1, LED15.1, LED16.1, LED17.1, LED18.1, LED19.1, LED20.1, LED21.1, LED22.1, LED23.1, LED24.1, LED25.1, LED26.1, LED27.1, LED28.1, LED29.1, LED30.1, LED31.1, R5.2, R7.2, S1.3 (NO_1), S1.7 (NO_3), S1.11 (NO_5), S1.15 (NO_7), S1.19 (NO_9), S1.23 (NO_11)
unnamed: D1.2, R1.1, R2.1, TP1.1
unnamed: IC3.7 (CIN), IC4.9 (COUT)
unnamed: C1.2, D1.1, IC5.1 (CP), R1.2
unnamed: LED1.2, R3.1
unnamed: LED2.2, R4.1
unnamed: LED3.2, R8.1
unnamed: LED4.2, R9.1
unnamed: LED5.2, R10.1
unnamed: LED6.2, R11.1
unnamed: LED7.2, R12.1
unnamed: LED8.2, R13.1
unnamed: LED9.2, R14.1
unnamed: LED10.2, R15.1
unnamed: LED11.2, R16.1
unnamed: LED12.2, R17.1
unnamed: LED13.2, R18.1
unnamed: LED14.2, R19.1
unnamed: LED15.2, R20.1
unnamed: LED16.2, R21.1
unnamed: LED17.2, R22.1
unnamed: LED18.2, R23.1
unnamed: LED19.2, R24.1
unnamed: LED20.2, R25.1
unnamed: LED21.2, R26.1
unnamed: LED22.2, R27.1
unnamed: LED23.2, R28.1
unnamed: LED24.2, R29.1
unnamed: LED25.2, R30.1
unnamed: LED26.2, R31.1
unnamed: LED27.2, R32.1
unnamed: LED28.2, R33.1
unnamed: LED29.2, R34.1
unnamed: LED30.2, R35.1
unnamed: LED31.2, R36.1
VCC: IC1.28 (VCC), IC2.28 (VCC), IC3.16 (VCC), IC4.16 (VCC), IC5.14 (VCC), IC6.20 (VCC), J4.1, R2.2, R6.2, S1.4 (NO_2), S1.8 (NO_4), S1.12 (NO_6), S1.16 (NO_8), S1.20 (NO_10), S1.24 (NO_12)
